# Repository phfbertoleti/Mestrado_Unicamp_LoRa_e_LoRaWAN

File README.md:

# Mestrado na FEEC (Unicamp) em redes sem fio, com foco em LoRa e LoRaWAN

Este repositório contendo todo o material que utilizei e gerei para meu mestado na FEEC (Unicamp), em redes sem fio com foco em LoRa e LoRaWAN.
Este repositório divide-se em três frentes: 

1. LoRa: na frente LoRa, é abordada a parte rádio propriamente dita, de forma a analisar o desempenho da interface de rádio LoRa em aplicações reais. 
2. LoRaWAN: na frente LoRaWAN, é abordado o uso de um gateway monocanal LoRaWAN, The Things Network (como Network Server e Application Server) e um end-device LoRaWAN, de forma a compor o nível 2 da TpM (Three-phase Methodology) para construção de soluções em Internet das Coisas.
3. Acessórios: disponibilização de modelos de impressão 3D, projeto de hardware e tudo mais relativo aos acessórios utilizados no desenvolvimento, testes e validações deste mestrado.

## Uso do repositório

Para melhor documentação, cada frente (LoRa e LoRaWAN) tem seu próprio README, com instruções do que existe de conteúdo e, quando aplicável, como usar em bancada a parte experimental / empírica do mestrado.

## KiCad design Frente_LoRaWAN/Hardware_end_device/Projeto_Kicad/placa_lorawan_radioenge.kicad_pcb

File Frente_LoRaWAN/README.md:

# Mestrado na FEEC (Unicamp) - frente LoRaWAN

Aqui encontra-se os dados, experimentos e materiais produzidos referentes a parte de LoRaWAN do meu mestrado.

## Conteúdo 1: end-device LoRaWAN

O end-device LoRaWAN contido aqui utiliza como hardware:

* Um ESP32 WROOM
* Um módulo LoRaWAN Radioenge (https://www.radioenge.com.br/produto/modulo-lorawan/ )
* Uma fonte 5V/2A (pode ser substituído por powerbank)

O end-device LoRaWAN, montado no projeto de PCB contido neste repositório, pode ser visto na figura abaixo:

Foto do end-device montado: 

A programação do end device pode ser feita de duas formas:

1. Via ESP-IDF com VSCode, extensão ESP-IDF e ESP-IDF versão 5.4.2. Nessa implementação, o end-device limita-se a enviar, a cada 30 minutos, os bytes fixos 0x01, 0x02 e 0x03 a cada 30 minutos.
Há planos de substituir os dados fixos (0x01, 0x02 e 0x03) pelo envio da leitura de uma entrada de tamper e também a leitura de uma distância medida por um sensor ultrasônico HC-SR04. Dessa forma, desde o momento atual, é preciso colocar no mesmo nível da pasta "end_device" a versão mais recente da lib https://github.com/UncleRus/esp-idf-lib .

2. Via Arduino IDE (versão da lib da placa ESP32: 2.0.17). Nessa implementação, o end-device limita-se a enviar, a cada minuto, os bytes fixos 0x01, 0x02 e 0x03.

Obervação: este end-device, em ambas implementações (ESP-IDF e Arduino) está preparado para operar na frequência de 916,8MHz e SF=7.

## Conteúdo 2: gateway LoRaWAN monocanal

O gateway LoRaWAN monocanal contido aqui deriva-se do seguinte projeto https://github.com/things4u/ESP-1ch-Gateway . Esta derivação contém algumas customizações para que o gateway melhor se adapte ao uo neste mestrado.
Este gateway é mostrado na figura abaixo:

Fotos dos gateways LoRaWAN monocanal feitos:

1. Versão com Heltec: 
2. Versão com ESP32 WROOM-32 e RF95: 

Este gateway pode utilizar como hardware:

* Uma placa Heltec WiFi LoRa V2, de frequência 868-915MHz OU um ESP32-WROOM 32 com rádio LoRa RF95
* Uma fonte 5V/2A

Para compilar e utilizar o gateway (independente do hardware utilizado), siga as instruções a seguir:

1. Na Arduino IDE, na tela de gerenciamento de placas, instale a versão 2.0.17 do esp32
2. Copie todas as bibliotecas / pastas em "libraries" para a pasta de bibliotecas Arduino do seu computador (exemplo: Documents\Arduino\libraries). Dessa forma, você possuirá todas as biblitoecas necessárias nas versões esperadas.
3. No arquivo configNode.h, altere a rede Wi-Fi (SSID) e senha da rede Wi-Fi na lista wpa. Se você quiser, pode adicionar quantas redes desejar nessa lista, de forma a conter redundâncias em caso de falha da rede Wi-Fi.
Após a alteração, o código do gateway pode ser compilado e, depois, gravado na placa Heltec WiFi LoRa V2. 
4. Quando o gateway inicializar, ele escreverá nas informações do Serial Monitor um ID (Gateway ID). Este ID corresponde ao endereço MAC do gateway, e deve ser usado na The Things Network (TTN) para cadastro do gateway no campo Gateway EUI.

Obervações: 
* Este gateway está preparado para operar na frequência de 916,8MHz e SF=7.
* Para abrigar este gateway LoRaWAN monocanal, foi utilizado o seguinte case, feito na impressora 3D: https://www.thingiverse.com/thing:6522462

## Conteúdo 3: TTN

Reune informações para conectar o gateway LoRaWAN monocanal a plataforma The Things Network (TTN), de forma a usar a plataforma como Application Server e Network Server.

## Vídeos explicativos

Para melhor exempificr como estabelecer o gateway LoRaWAN monocanal e o end-device LoRaWAN, existem os seguintes vídeos:

* *Gateway LoRaWAN monocanal:* explicação de parametrização de software, compilação e gravação Heltec WiFi LoRa V2: https://drive.google.com/file/d/1u9MdMoPO0pTy7fwZNUEaMupEhpbTwCIz/view?usp=sharing

* *End-device:* explicação do hardware e breve explicação da integração com The Things Network: https://drive.google.com/file/d/1UwrbAW2tfpAEE6ByUf8U8BOljeANyCgI/view?usp=sharing

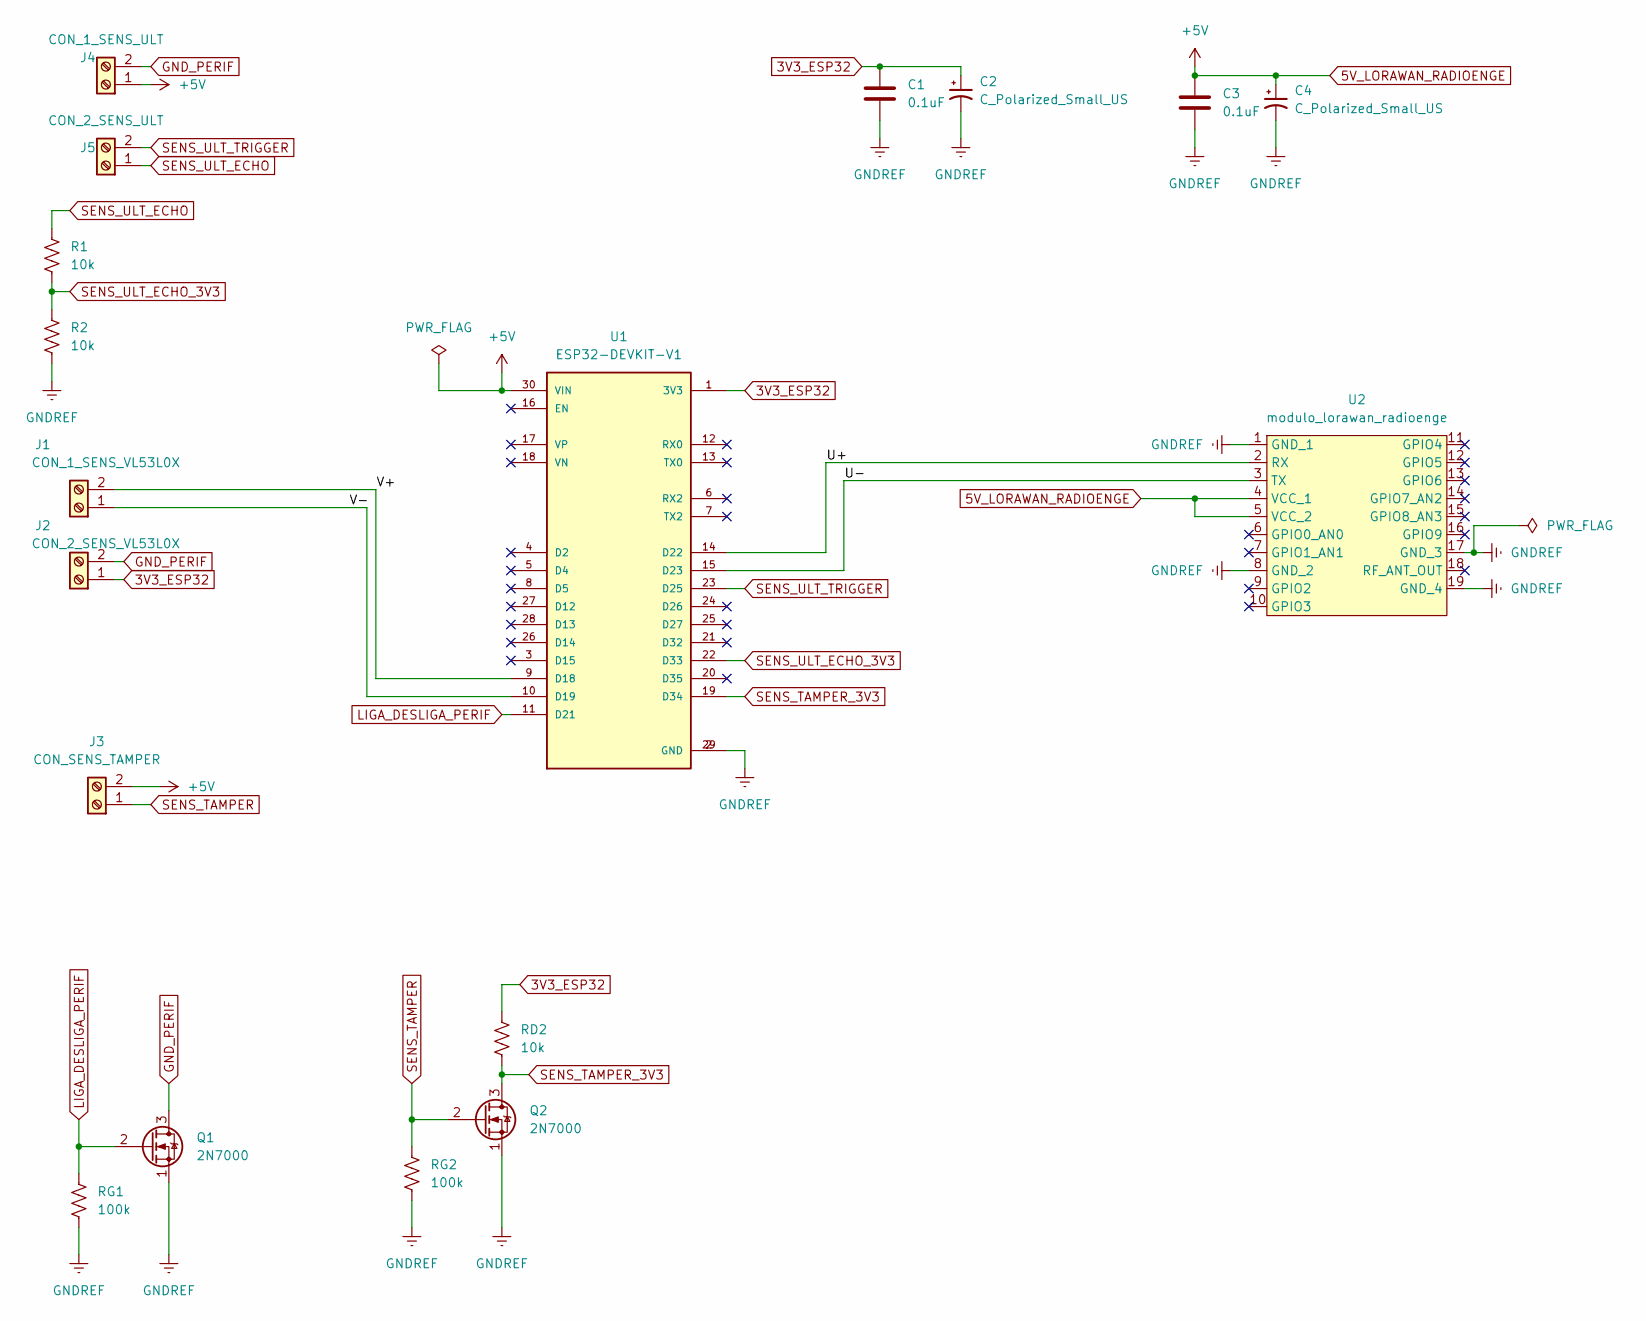
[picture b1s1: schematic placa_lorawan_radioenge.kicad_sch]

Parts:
C1, C3: 0.1uF; C_Disc_D6.0mm_W2.5mm_P5.00mm
C2, C4: C_Polarized_Small_US; CP_Radial_Tantal_D4.5mm_P5.00mm
J1: CON_1_SENS_VL53L0X; PhoenixContact_MCV_1,5_2-G-5.08_1x02_P5.08mm_Vertical
J2: CON_2_SENS_VL53L0X; PhoenixContact_MCV_1,5_2-G-5.08_1x02_P5.08mm_Vertical
J3: CON_SENS_TAMPER; PhoenixContact_MCV_1,5_2-G-5.08_1x02_P5.08mm_Vertical
J4: CON_1_SENS_ULT; PhoenixContact_MCV_1,5_2-G-5.08_1x02_P5.08mm_Vertical
J5: CON_2_SENS_ULT; PhoenixContact_MCV_1,5_2-G-5.08_1x02_P5.08mm_Vertical
Q1, Q2: 2N7000; TO-92_Inline
R1, R2: 10k; R_Axial_DIN0204_L3.6mm_D1.6mm_P7.62mm_Horizontal
RD2: 10k; R_Axial_DIN0204_L3.6mm_D1.6mm_P7.62mm_Horizontal
RG1, RG2: 100k; R_Axial_DIN0204_L3.6mm_D1.6mm_P7.62mm_Horizontal
U1: ESP32-DEVKIT-V1; MODULE_ESP32_DEVKIT_V1; PARTREV N/A
U2: modulo_lorawan_radioenge; mod_lorawan_radioenge

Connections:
3V3_ESP32: C1.1, C2.1, J2.1, RD2.1, U1.1 (3V3)
5V_LORAWAN_RADIOENGE: C3.1, C4.1, J3.2, J4.1, U1.30 (VIN), U2.4 (VCC_1), U2.5 (VCC_2)
/U+: U1.14 (D22), U2.2 (RX)
/U-: U1.15 (D23), U2.3 (TX)
/V+: J1.2, U1.9 (D18)
/V-: J1.1, U1.10 (D19)
GNDREF: C1.2, C2.2, C3.2, C4.2, Q1.1 (S), Q2.1 (S), R2.2, RG1.2, RG2.2, U1.2 (GND), U1.29 (GND), U2.1 (GND_1), U2.8 (GND_2), U2.17 (GND_3), U2.19 (GND_4)
GND_PERIF: J2.2, J4.2, Q1.3 (D)
LIGA_DESLIGA_PERIF: Q1.2 (G), RG1.1, U1.11 (D21)
SENS_TAMPER: J3.1, Q2.2 (G), RG2.1
SENS_TAMPER_3V3: Q2.3 (D), RD2.2, U1.19 (D34)
SENS_ULT_ECHO: J5.1, R1.1
SENS_ULT_ECHO_3V3: R1.2, R2.1, U1.22 (D33)
SENS_ULT_TRIGGER: J5.2, U1.23 (D25)

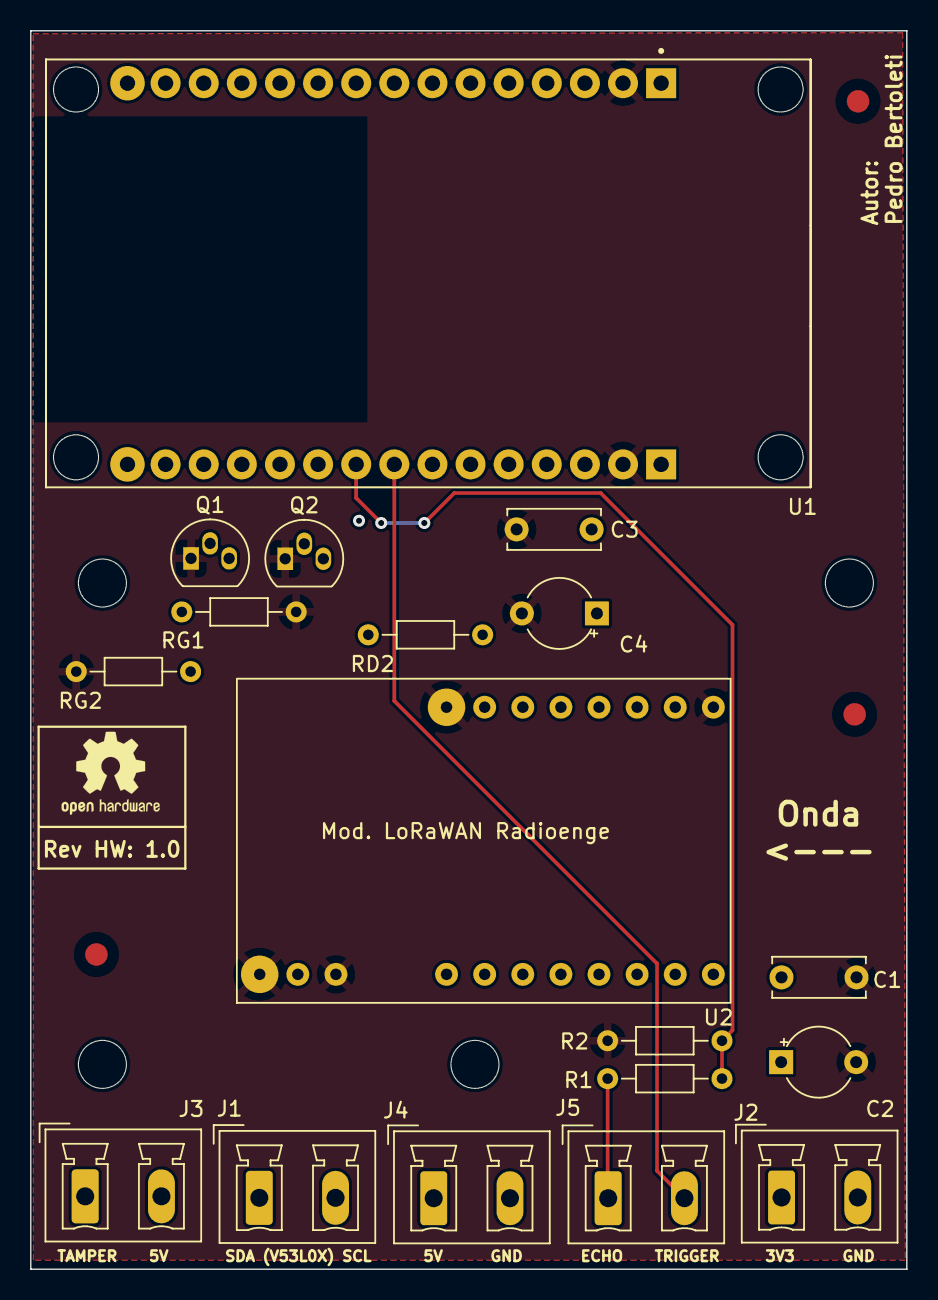
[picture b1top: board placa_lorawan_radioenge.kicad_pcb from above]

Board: 4 copper layers, 58.4 x 82.5 mm, 25 parts (0 on the bottom side), 14 nets.

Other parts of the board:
 : MountingHole_3.2mm_M3
 #2,  #3,  #4: MountingHole_3.2mm_M3
 #5,  #6,  #7: Fiducial_1.5mm_Mask3mm

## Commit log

2025-08-18 Primeiro commit
2025-08-18 Adicionado: projeto da placa do end-device LoRaWAN
2025-09-05 Adição: dois vídeos explicativos (sobre Gateway LoRaWAN monocanal e end-device)
2025-09-08 Adição: versão da biblioteca da placa ESP32
2025-09-08 Adição: pasta de acessórios usados na tese e primeiro acessório disponibilizado: base para antena SMA (polarizações horizontal e vertical
2025-09-08 Adição: README dos acessórios. Edição: README geral do repositório
2025-09-08 Adição: foto da base SMA com polarizações de antena (vertical e horizontal)
2025-09-08 Adição: exibição da foto da base SMA no README de acessórios
2025-09-11 Adição: fotos do gateway LoRaWAN monocanal e end-device LoRaWAN
2025-09-11 Adição: fotos do end-device LoRaWAN
2025-10-22 Adicionado exemplo de end-device LoRaWAN com Arduino feito por Lucas Fernandes (lucasfernandes94lf@gmail.com). Adicionadas fotos do gateway LoRaWAN monicanal feito com RF95.
2025-10-22 Atualizacao do README da frente LoRaWAN
2025-11-22 Adicionado: roteiro de uso da TTN com gateway LoRaWAN monocanal. Também foi atualizado o README da frente LoRaWAN
